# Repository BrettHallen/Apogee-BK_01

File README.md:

# Апогей БК 01/Apogee BK 01
Information about the Soviet Apogee BK 01 computer, an implementation of the Радио 86РК/Radio 86RK design.

## [New Power Supply](/Apogee-BK_01_Power)
As the Apogee uses the 8080 it requries a tri-voltage power supply, ±5VDC and +12VDC, via a 7-pin DIN.  This is my simple implementation of a replacement using a single +12VDC power source, generating the ±5V via two switching regulators.<br>

- Pin 1 = +5V regulated
- Pin 2 = +5V regulated
- Pin 3 = +12V regulated
- Pin 4 = -5V unregulated
- Pin 5 = ground (общий)
- Pin 6 = ground (общий)
- Pin 7 = fault (авария)

The fault/авария signal on the motherboard monitors the +5V rail relative to the -5V rail.  If the +5V rail drifts too far out of range (over/undervoltage) then it will signal the power supply to shut off the linear regulators (КР142ЕН1Б, similar to Western UA723).

## [Schematics](/Schematics)
High quality scans of the original schematics.

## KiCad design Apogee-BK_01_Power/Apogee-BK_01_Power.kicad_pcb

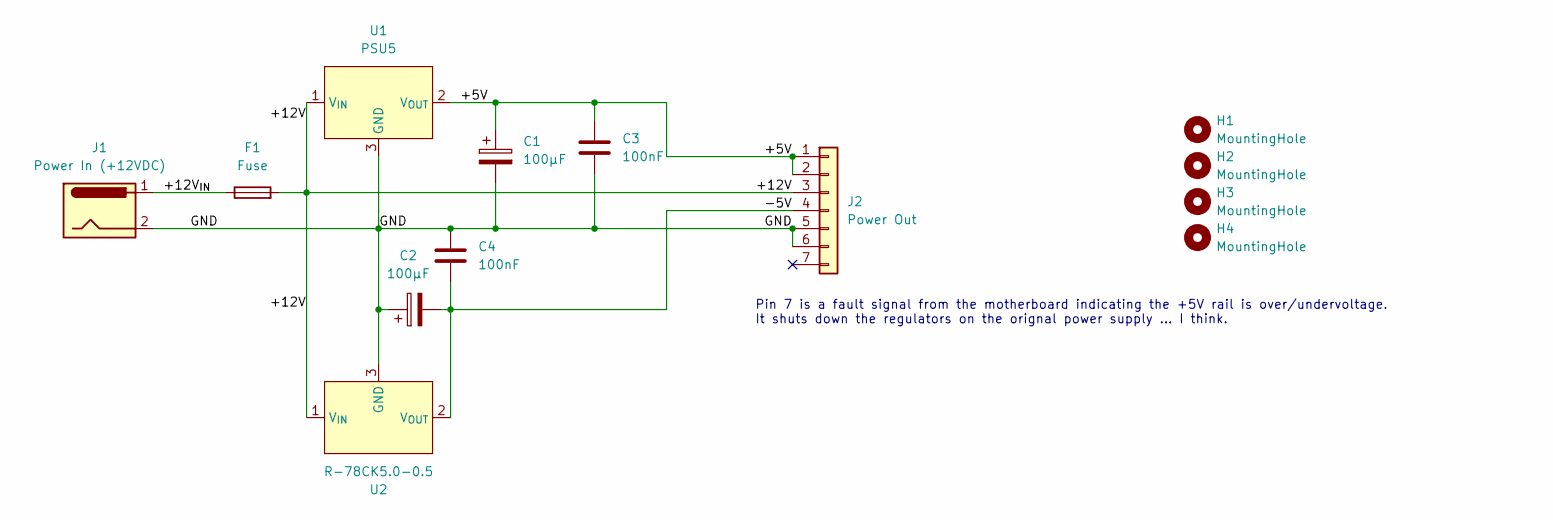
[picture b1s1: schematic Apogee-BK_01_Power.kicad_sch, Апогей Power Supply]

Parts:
C1, C2: 100µF; CP_Radial_D6.3mm_P2.50mm
C3, C4: 100nF; C_Disc_D3.8mm_W2.6mm_P2.50mm
F1: Fuse; Fuseholder_Clip-5x20mm_Littelfuse_111_Inline_P20.00x5.00mm_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
H1, H2, H3, H4: MountingHole; MountingHole_3.2mm_M3_DIN965
J1: Power In (+12VDC); BarrelJack_CUI_PJ-063AH_Horizontal
J2: Power Out; 6710801
U1: PSU5; TO-3
U2: R-78CK5.0-0.5; TO-220-3_Vertical; Manufacturer_Part_Number R-78CK5.0-0.5

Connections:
/+5V: C1.1, C3.1, J2.1, J2.2, U1.2 (V_{OUT})
/+12V: F1.2, J2.3, U1.1 (V_{IN}), U2.1 (V_{IN})
/+12V_{IN}: F1.1, J1.1
/-5V: C2.2, C4.1, J2.4, U2.2 (V_{OUT})
/GND: C1.2, C2.1, C3.2, C4.2, J1.2, J2.5, J2.6, U1.3 (GND), U2.3 (GND)

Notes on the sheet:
Pin 7 is a fault signal from the motherboard indicating the +5V rail is over/undervoltage. It shuts down the regulators on the orignal power supply ... I think.

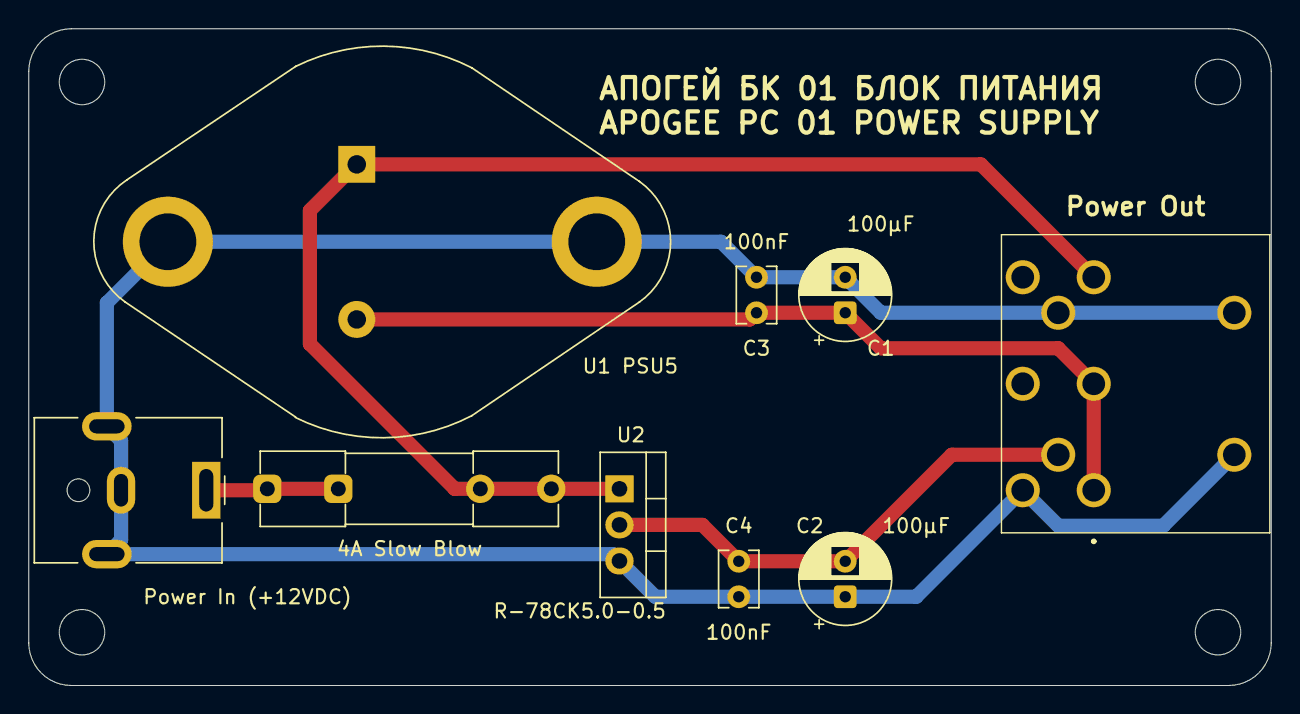
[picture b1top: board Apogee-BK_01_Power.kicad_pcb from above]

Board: 2 copper layers, 87.5 x 46.2 mm, 13 parts (0 on the bottom side), 5 nets.

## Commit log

2026-03-04 Scans of schematics
2026-03-14 Added fuse to 12V input rail
